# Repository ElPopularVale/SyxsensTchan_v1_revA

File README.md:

KiCad Project for an Extensible SAMD21 LoRa sensor node with crypto chip, RGB LED, USB-C and flash codenamed "Syxsens T-Chain".

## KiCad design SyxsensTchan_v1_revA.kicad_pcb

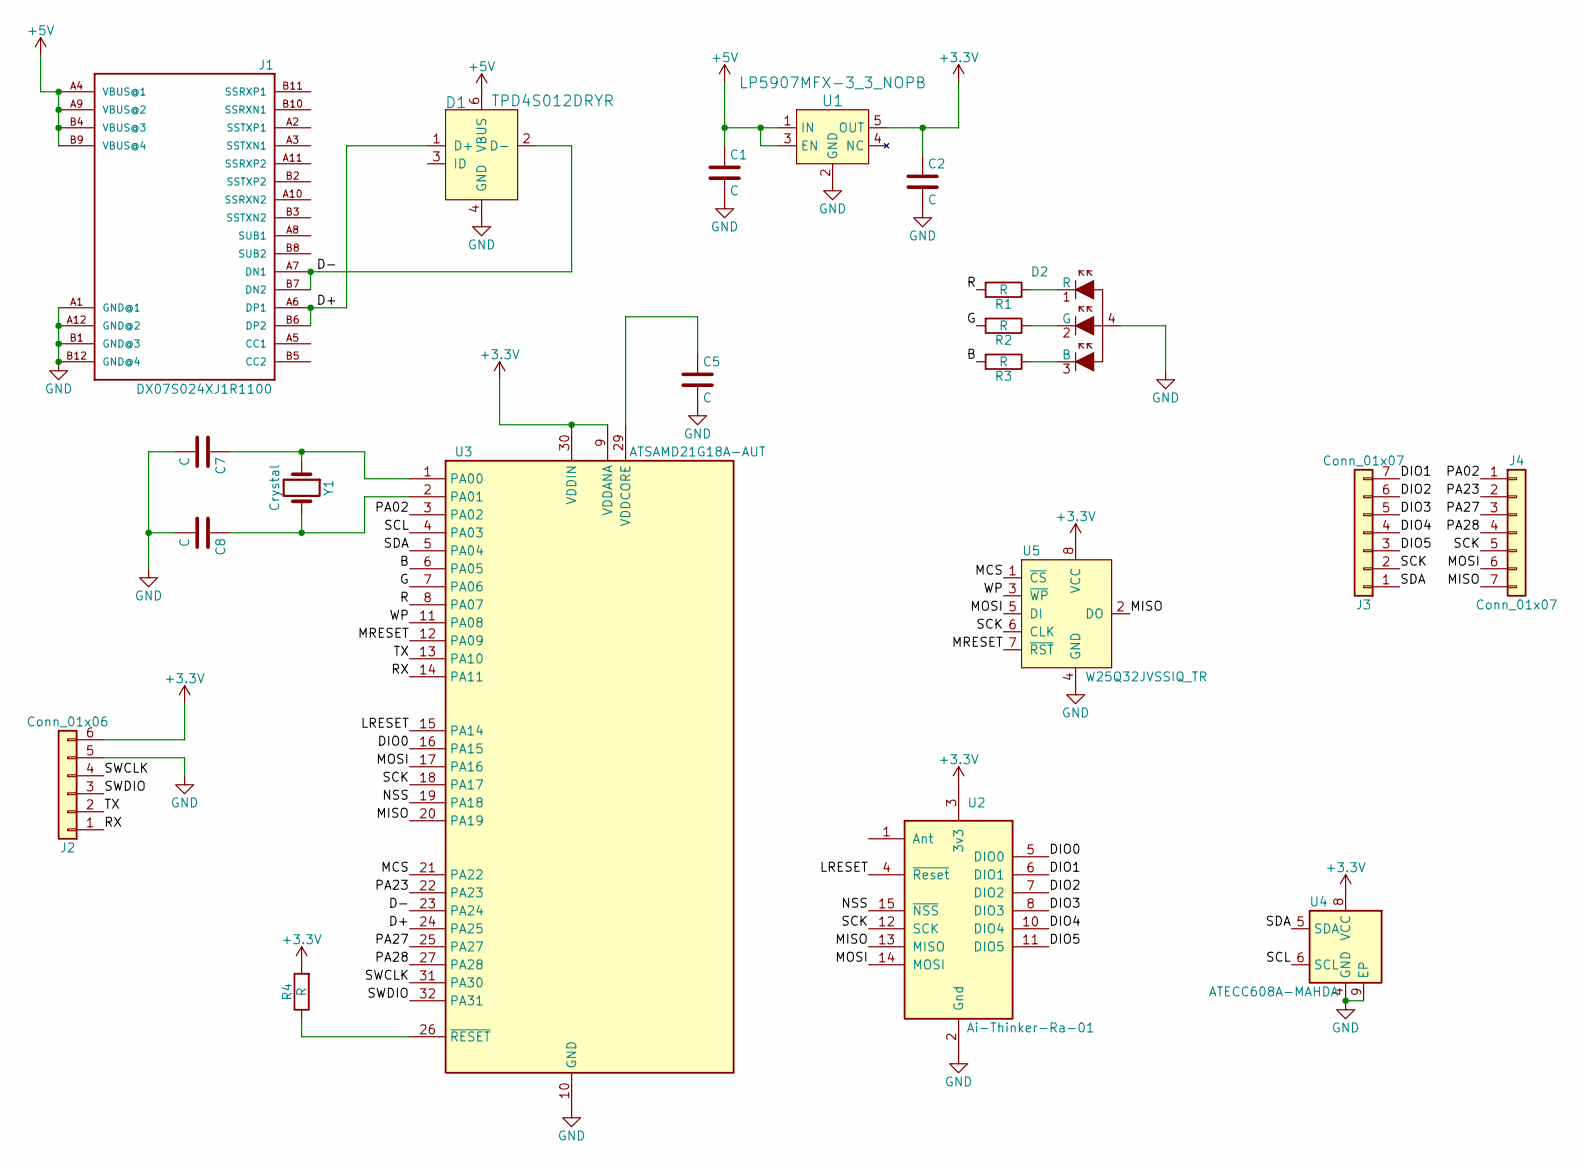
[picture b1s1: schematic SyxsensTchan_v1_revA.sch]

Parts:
C1, C2, C5, C7, C8: C; C_0402_1005Metric
D1: TPD4S012DRYR; Fairchild_MicroPak-6_1.0x1.45mm_P0.5mm; MPN TPD4S012DRYR; Digi-Key_PN 296-24244-1-ND
D2: LTST-C19HE1WT; LED_Dual0603; MPN LTST-C19HE1WT; Digi-Key_PN 160-2162-1-ND
J1: DX07S024XJ1R1100; JAE_DX07S024XJ1R1100
J2: Conn_01x06; 1.27mm_pads_01x06
J3, J4: Conn_01x07; PinSocket_1x07_P2.54mm_Vertical
R1, R2, R3, R4: R; R_0402_1005Metric
U1: LP5907MFX-3_3_NOPB; SOT-23-5; MPN LP5907MFX-3.3/NOPB; Digi-Key_PN 296-38557-1-ND
U2: Ai-Thinker-Ra-01; Ai-Thinker-Ra-01-LoRa
U3: ATSAMD21G18A-AUT; QFN-32-1EP_5x5mm_P0.5mm_EP3.6x3.6mm
U4: ATECC608A-MAHDA; DFN-8-1EP_3x2mm_P0.5mm_EP1.3x1.5mm
U5: W25Q32JVSSIQ_TR; SOIC-8_5.23x5.23mm_P1.27mm; MPN W25Q32JVSSIQ TR; Digi-Key_PN W25Q32JVSSIQCT-ND
Y1: Crystal; ABS05-32.768KHZ-T

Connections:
+3V3: C2.1, J2.6, R4.2, U1.5 (OUT), U2.3 (3v3), U3.9 (VDDANA), U3.30 (VDDIN), U4.8 (VCC), U5.8 (VCC)
+5V: C1.1, D1.6 (VBUS), J1.A4 (VBUS@1), J1.A9 (VBUS@2), J1.B4 (VBUS@3), J1.B9 (VBUS@4), U1.1 (IN), U1.3 (EN)
/B: R3.2, U3.6 (PA05)
/D+: D1.1 (D+), J1.A6 (DP1), J1.B6 (DP2), U3.24 (PA25)
/D-: D1.2 (D-), J1.A7 (DN1), J1.B7 (DN2), U3.23 (PA24)
/DIO0: U2.5 (DIO0), U3.16 (PA15)
/DIO1: J3.7, U2.6 (DIO1)
/DIO2: J3.6, U2.7 (DIO2)
/DIO3: J3.5, U2.8 (DIO3)
/DIO4: J3.4, U2.10 (DIO4)
/DIO5: J3.3, U2.11 (DIO5)
/G: R2.2, U3.7 (PA06)
/LRESET: U2.4 (~Reset), U3.15 (PA14)
/MCS: U3.21 (PA22), U5.1 (~CS)
/MISO: J4.7, U2.13 (MISO), U3.20 (PA19), U5.2 (DO)
/MOSI: J4.6, U2.14 (MOSI), U3.17 (PA16), U5.5 (DI)
/MRESET: U3.12 (PA09), U5.7 (~RST)
/NSS: U2.15 (~NSS), U3.19 (PA18)
/PA02: J4.1, U3.3 (PA02)
/PA23: J4.2, U3.22 (PA23)
/PA27: J4.3, U3.25 (PA27)
/PA28: J4.4, U3.27 (PA28)
/R: R1.2, U3.8 (PA07)
/RX: J2.1, U3.14 (PA11)
/SCK: J3.2, J4.5, U2.12 (SCK), U3.18 (PA17), U5.6 (CLK)
/SCL: U3.4 (PA03), U4.6 (SCL)
/SDA: J3.1, U3.5 (PA04), U4.5 (SDA)
/SWCLK: J2.4, U3.31 (PA30)
/SWDIO: J2.3, U3.32 (PA31)
/TX: J2.2, U3.13 (PA10)
/WP: U3.11 (PA08), U5.3 (~WP)
GND: C1.2, C2.2, C5.2, C7.2, C8.2, D1.4 (GND), D2.4, J1.A1 (GND@1), J1.A12 (GND@2), J1.B1 (GND@3), J1.B12 (GND@4), J2.5, U1.2 (GND), U2.2 (Gnd), U2.9 (Gnd), U2.16 (Gnd), U3.10 (GND), U3.28 (GND), U4.4 (GND), U4.9 (EP), U5.4 (GND)
unnamed: C5.1, U3.29 (VDDCORE)
unnamed: C7.1, U3.1 (PA00), Y1.1
unnamed: C8.1, U3.2 (PA01), Y1.2
unnamed: D2.1 (R), R1.1
unnamed: D2.2 (G), R2.1
unnamed: D2.3 (B), R3.1
unnamed: R4.1, U3.26 (~RESET)

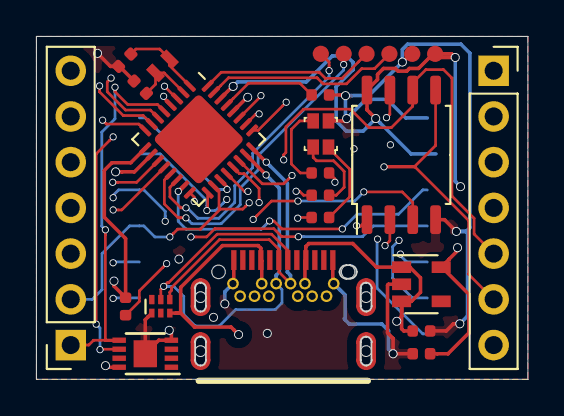
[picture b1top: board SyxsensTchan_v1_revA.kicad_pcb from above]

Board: 4 copper layers, 27.3 x 19.0 mm, 21 parts (1 on the bottom side), 39 nets.
